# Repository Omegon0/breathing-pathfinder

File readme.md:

# Breathing device

I built this so that I can relax by syncing my breathing with the device that i've built. It uses a button to control the speed of breathing and it uses 6 LEDs to indicate the speed setting. The LEDs will pulse at the speed (1 slowest 6 fastest). 

It's a very simple device.

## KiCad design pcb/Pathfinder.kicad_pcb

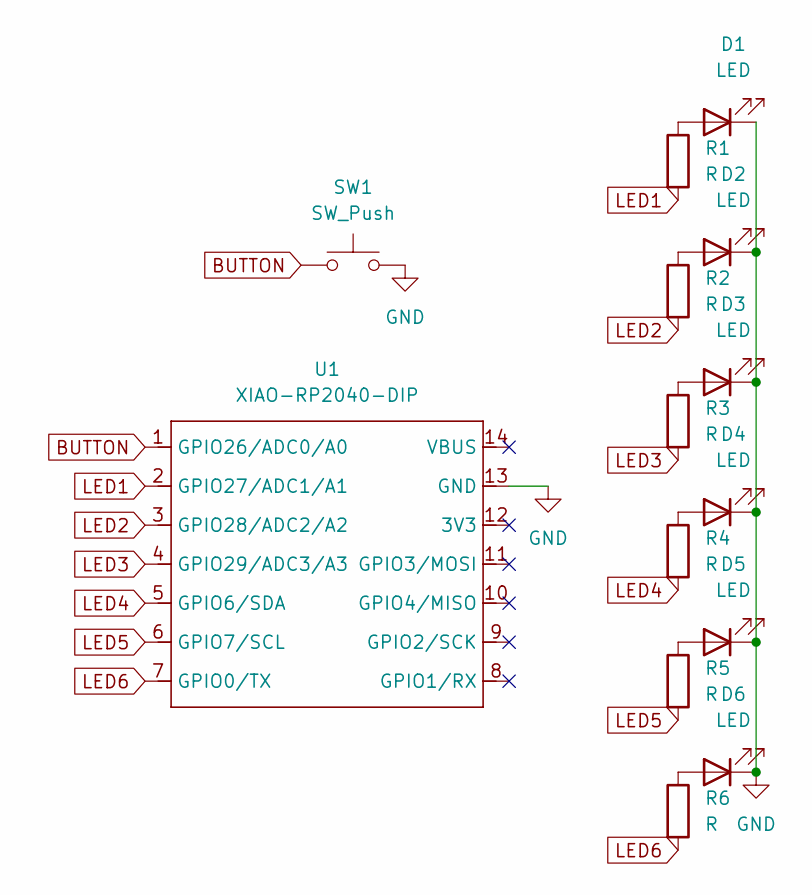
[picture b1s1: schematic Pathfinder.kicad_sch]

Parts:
D1, D2, D3, D4, D5, D6: LED; LEDRD254W57D500H1070
R1, R2, R3, R4, R5, R6: R; R_Axial_DIN0204_L3.6mm_D1.6mm_P5.08mm_Horizontal
SW1: SW_Push; SW_Cherry_MX_1.00u_PCB
U1: XIAO-RP2040-DIP

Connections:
BUTTON: SW1.1, U1.1 (GPIO26/ADC0/A0)
GND: D1.1 (K), D2.1 (K), D3.1 (K), D4.1 (K), D5.1 (K), D6.1 (K), SW1.2, U1.13 (GND)
LED1: R1.2, U1.2 (GPIO27/ADC1/A1)
LED2: R2.2, U1.3 (GPIO28/ADC2/A2)
LED3: R3.2, U1.4 (GPIO29/ADC3/A3)
LED4: R4.2, U1.5 (GPIO6/SDA)
LED5: R5.2, U1.6 (GPIO7/SCL)
LED6: R6.2, U1.7 (GPIO0/TX)
unnamed: D1.2 (A), R1.1
unnamed: D2.2 (A), R2.1
unnamed: D3.2 (A), R3.1
unnamed: D4.2 (A), R4.1
unnamed: D5.2 (A), R5.1
unnamed: D6.2 (A), R6.1

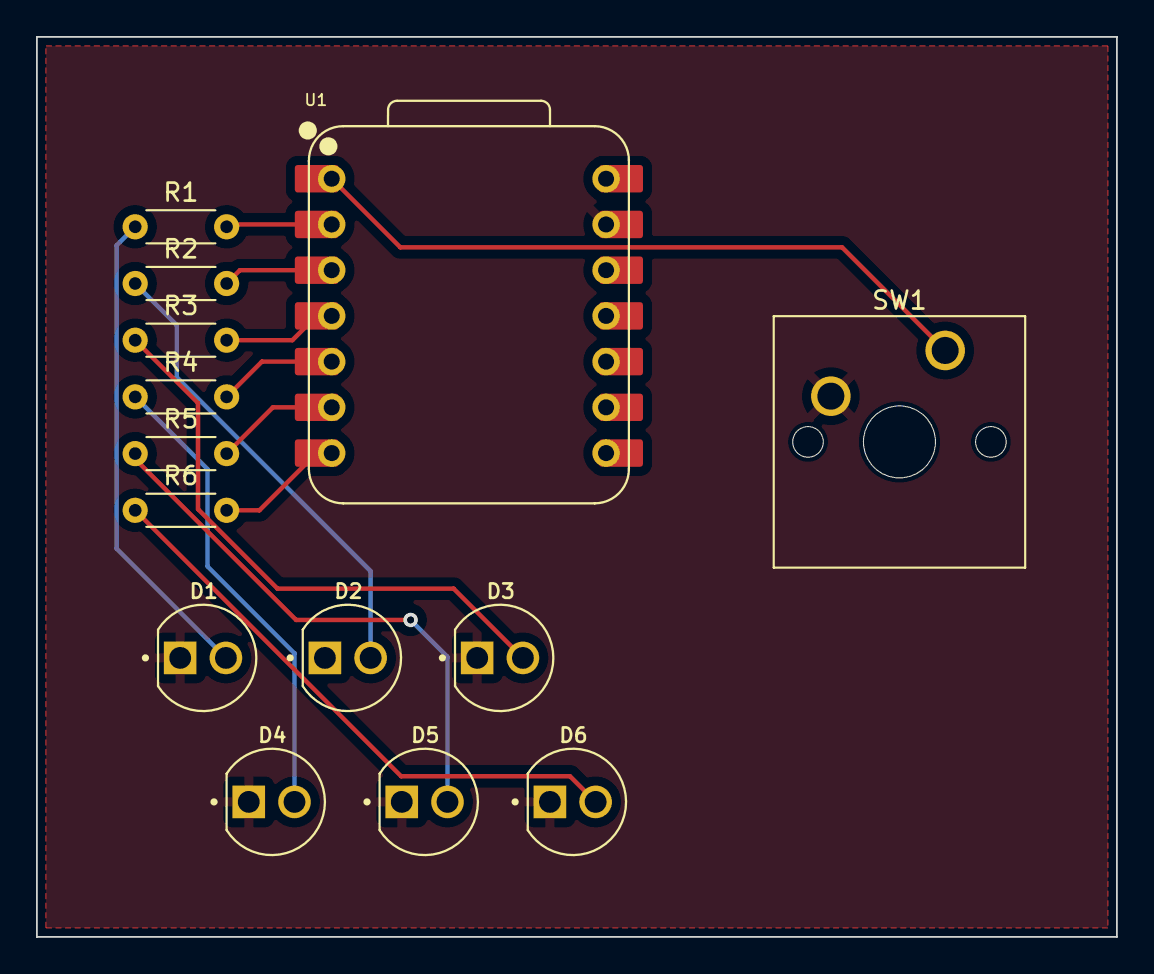
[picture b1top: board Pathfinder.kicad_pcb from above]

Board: 2 copper layers, 60.0 x 50.0 mm, 14 parts (0 on the bottom side), 14 nets.

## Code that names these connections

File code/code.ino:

int BUT = D0;

int LED1 = D3;
int LED2 = D4;
int LED3 = D5;
int LED4 = D3;
int LED5 = D4;
int LED6 = D5;

int speed = 1;

void setup() {
  pinMode(BUT, INPUT_PULLUP);

  pinMode(LED1, OUTPUT);
  pinMode(LED2, OUTPUT);
  pinMode(LED3, OUTPUT);
  pinMode(LED4, OUTPUT);
  pinMode(LED5, OUTPUT);
  pinMode(LED6, OUTPUT);
}

void breathe() {
  digitalWrite((int) (255 * sin(speed * millis())), LED1);
  if(speed > 1) digitalWrite((int) (255 * sin(speed * millis())), LED2);
  if(speed > 2) digitalWrite((int) (255 * sin(speed * millis())), LED3);
  if(speed > 3) digitalWrite((int) (255 * sin(speed * millis())), LED4);
  if(speed > 4) digitalWrite((int) (255 * sin(speed * millis())), LED5);
  if(speed > 5) digitalWrite((int) (255 * sin(speed * millis())), LED6);
}

void loop() {
  if(digitalRead(BUT) == HIGH) speed += 1;
  if(speed > 6) speed = 1;

  breathe();
}

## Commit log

2025-07-29 added everything
2025-07-29 fixed images
